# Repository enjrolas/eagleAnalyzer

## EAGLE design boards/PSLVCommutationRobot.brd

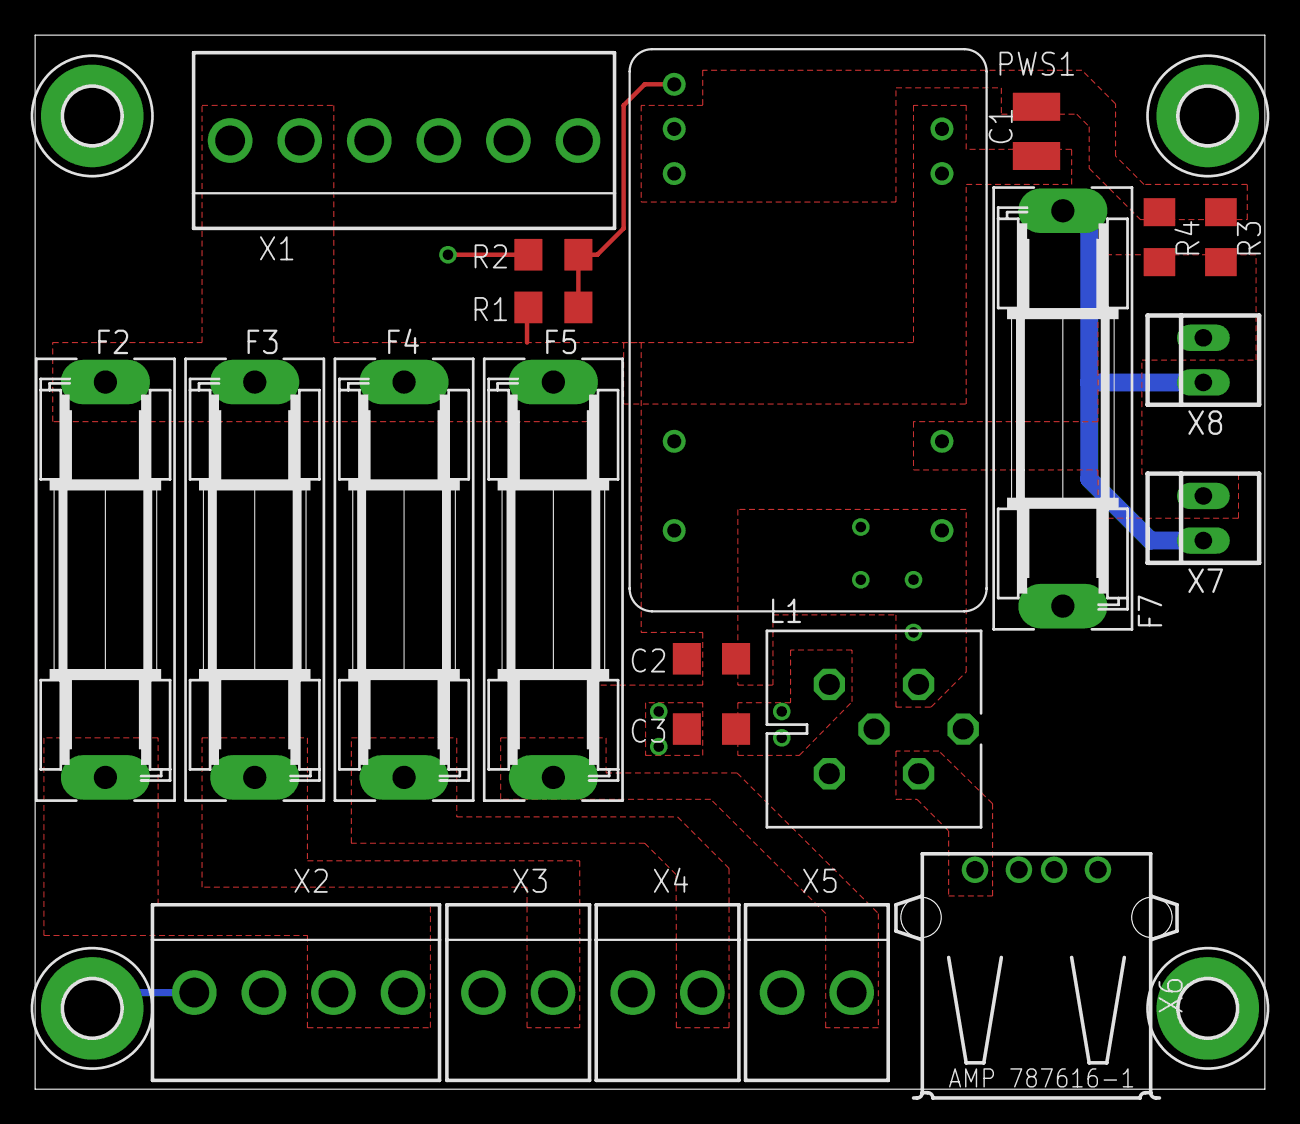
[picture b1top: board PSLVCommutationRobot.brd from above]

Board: 2 copper layers, 70.0 x 60.0 mm, 26 parts (0 on the bottom side), 12 nets.

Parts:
C1: 1uF 50V; C1210
C2, C3: 1nF 2KV; C1206
F2, F3, F4, F5: FH-102; SH22,5
F7: SH22,5
H1, H2, H3, H4: MOUNT-PAD-ROUND3.3; 3,3-PAD
L1: BNX002
PWS1: TEN_8-2411; TRACO_TEN_8_SERIE
R1, R2: 1M 5%; R1206
R3, R4: 0R; R1206
X1: 09-65-2068; MOLEX_09-65-2068
X2: 09-65-2048; MOLEX_09-65-2048
X3, X4, X5: 09-65-2028; MOLEX_09-65-2028
X6: USB type A; USB
X7, X8: 22-23-2021

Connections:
+5V: L1.CB, X6.1
+5V_OUT: C2.2, F7.1, L1.B, PWS1.14
+24V_IN: C1.1, C2.1, F2.1, F3.1, F4.1, F5.1, PWS1.22, PWS1.23, R1.1, X1.1, X1.2
GND: C1.2, C3.1, H4.B3,3, PWS1.2, PWS1.3, R2.2, R3.1, R4.1, X1.3, X1.4, X2.3, X2.4, X3.2, X4.2, X5.2
GND1: L1.CG, L1.CG1, L1.CG2, X6.4
GND_OUT: C3.2, L1.PSG, PWS1.16, R3.2, R4.2, X7.2, X8.2
unnamed: PWS1.1, R1.2, R2.1
unnamed: F2.2, X2.1, X2.2
unnamed: F3.2, X3.1
unnamed: F7.2, X7.1, X8.1
unnamed: F5.2, X5.1
unnamed: F4.2, X4.1

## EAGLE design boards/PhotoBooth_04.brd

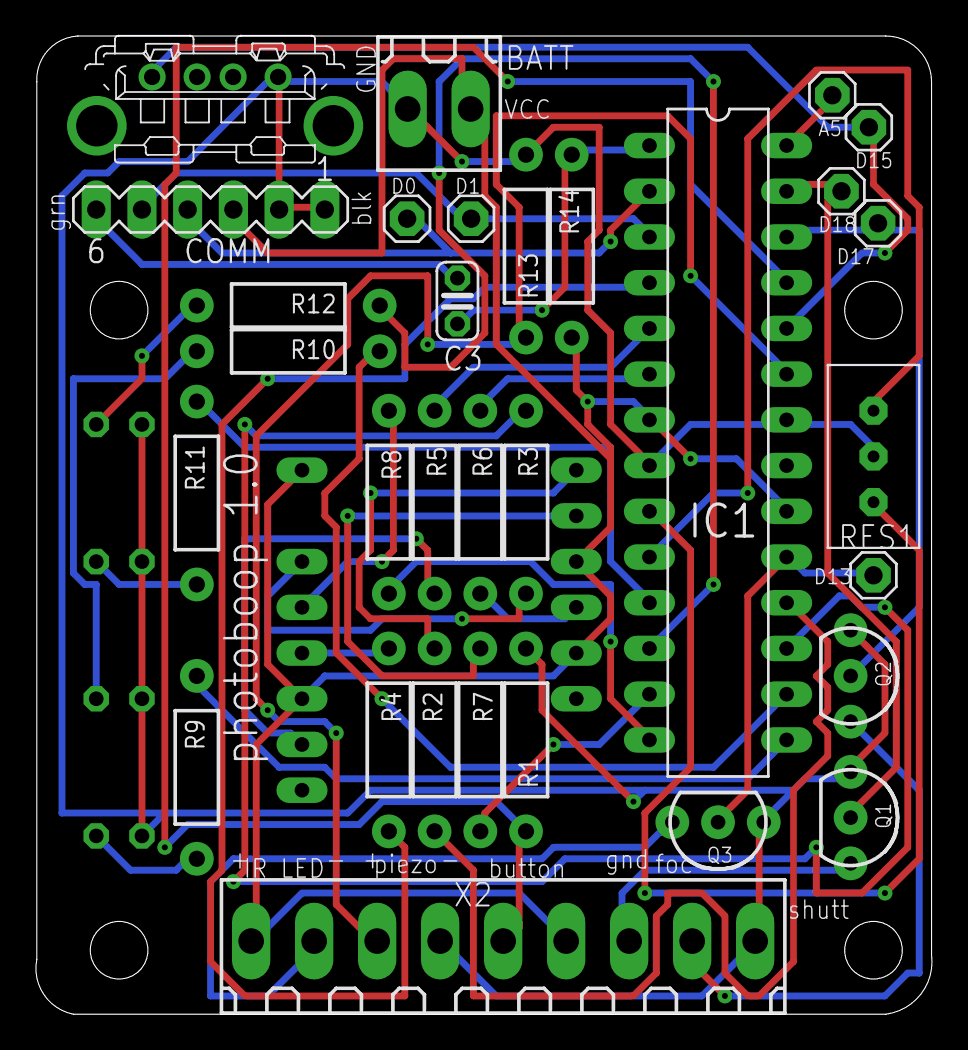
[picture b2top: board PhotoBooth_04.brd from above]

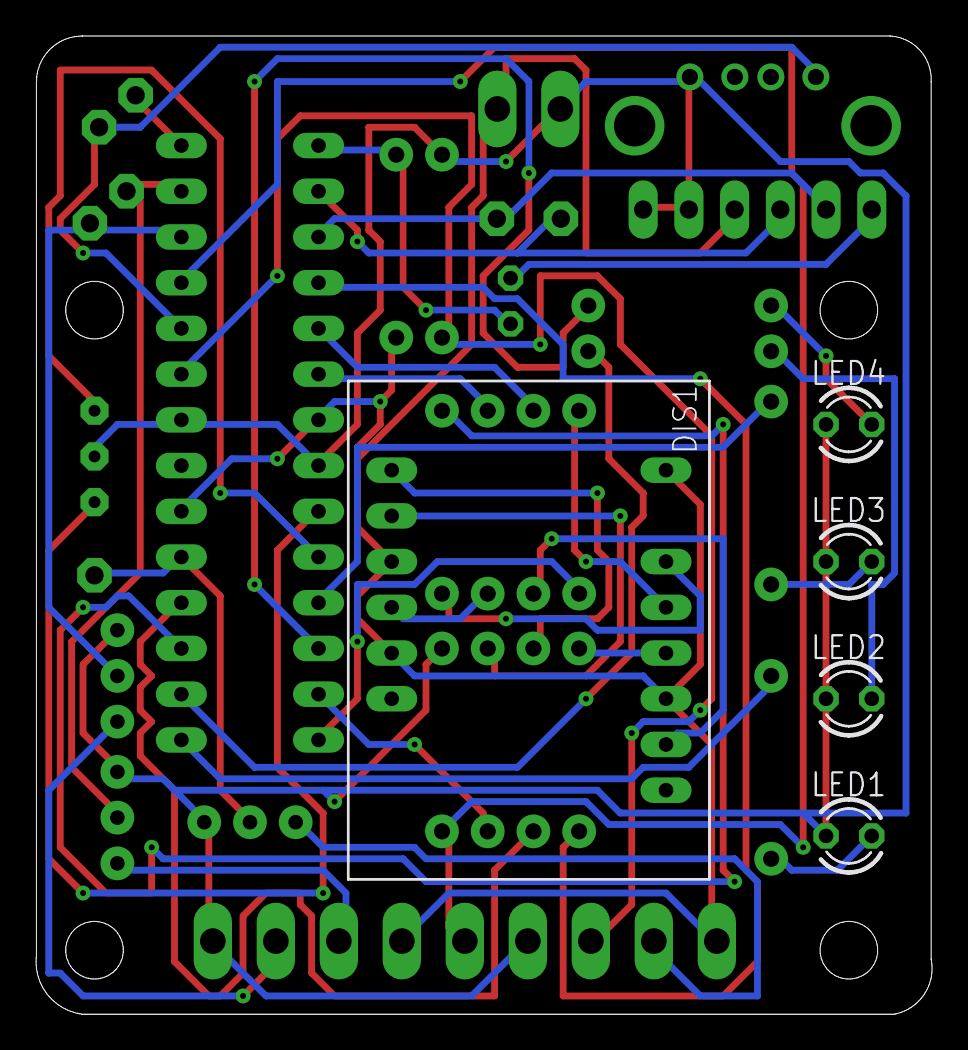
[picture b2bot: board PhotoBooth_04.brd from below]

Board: 2 copper layers, 49.8 x 54.3 mm, 36 parts (5 on the bottom side), 40 nets.

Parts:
A5: 1X01
BATT: 180-2
C3: 0.1uF; C025-024X044
COMM: MA06-1
D0, D1, D13, D15, D17, D18: 1X01
DIS1: HD-N105; HDSP-Q
IC1: ATMEGA328-P; DIL28-3
LED1, LED2, LED3, LED4: LED3MM
Q1, Q2, Q3: 2N3904; TO-92-AMMO
R1, R14: 10k; AXIAL-0.4
R2, R3, R4, R5, R6, R7, R8, R9, R10, R11, R12: 220; AXIAL-0.4
R13: 10M; AXIAL-0.4
RES1: RESONZTT
X1: USBVX; KUSBVX
X2: 180-9

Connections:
A_SEGMENT: IC1.18, R2.P$2
BUTTON: IC1.25, R1.P$1, X2.5
B_SEGMENT: IC1.17, R3.P$2
CAMERA: D15.1, IC1.24, X1.1
C_SEGMENT: IC1.4, R4.P$2
DIR: C3.1, COMM.6
D_SEGMENT: IC1.5, R5.P$2
E_SEGMENT: IC1.6, R6.P$2
F_SEGMENT: IC1.13, R7.P$2
GND: BATT.2, COMM.1, COMM.2, IC1.8, IC1.22, LED1.K, LED2.K, LED3.K, LED4.K, Q1.1, Q2.1, Q3.1, R1.P$2, R13.P$2, RES1.2, X1.4, X2.4, X2.9
G_SEGMENT: IC1.14, R8.P$2
IR_LED: D13.1, IC1.19, Q3.2
unnamed: LED1.A, R9.P$2
unnamed: DIS1.14, R8.P$1
unnamed: DIS1.3, R7.P$1
unnamed: DIS1.5, R6.P$1
unnamed: DIS1.11, R5.P$1
unnamed: DIS1.13, R4.P$1
unnamed: LED2.A, R10.P$2
unnamed: DIS1.15, R3.P$1
unnamed: DIS1.2, R2.P$1
unnamed: LED3.A, R11.P$2
unnamed: LED4.A, R12.P$2
unnamed: Q1.3, X2.7
unnamed: IC1.10, RES1.1
unnamed: IC1.9, RES1.3
unnamed: C3.2, IC1.1, R14.P$2
unnamed: A5.1, IC1.28
unnamed: Q2.3, X2.8
unnamed: Q3.3, X2.2
unnamed: COMM.4, D0.1, IC1.2
unnamed: COMM.5, D1.1, IC1.3
NUM1: IC1.15, R9.P$1
NUM2: IC1.16, R10.P$1
NUM3: IC1.11, R11.P$1
NUM4: IC1.12, R12.P$1
PIEZO: IC1.23, R13.P$1, X2.3
VCC: BATT.1, COMM.3, DIS1.4, DIS1.6, DIS1.12, DIS1.17, IC1.7, IC1.20, R14.P$1, X2.1, X2.6
WIRED_FOCUS: D17.1, IC1.26, Q2.2
WIRED_SHUTTER: D18.1, IC1.27, Q1.2

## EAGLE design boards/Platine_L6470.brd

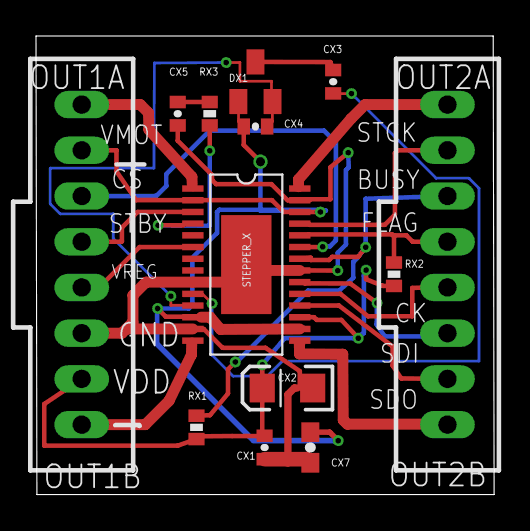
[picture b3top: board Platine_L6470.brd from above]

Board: 2 copper layers, 25.5 x 25.5 mm, 13 parts (0 on the bottom side), 21 nets.

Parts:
CX1: 0.1uF; 0402-CAP
CX2: 10uF; EIA3216
CX3, CX4, CX5: 10nF; 0402-CAP
CX7: 0.22uF; 0603-CAP
DX1: BAV99; SOT23
RX1, RX2: 10k; 0402-RES
RX3: 100; 0402-RES
STEPPER_X: L6470; HTSSOP28
X1, X2: C-GRID-08-70543; 70543-08

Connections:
BUSYN: RX1.1, STEPPER_X.22, X2.3
CK: STEPPER_X.19, X2.5
CSN: STEPPER_X.23, X1.3
FLAGN: RX2.1, STEPPER_X.24, X2.4
GND: CX1.2, CX2.C, CX5.2, CX7.2, STEPPER_X.9, STEPPER_X.13, STEPPER_X.21, STEPPER_X.27, STEPPER_X.29, X1.6
unnamed: CX3.2, STEPPER_X.10
unnamed: CX3.1, DX1.3
unnamed: CX4.1, DX1.2, STEPPER_X.11
unnamed: RX3.1, STEPPER_X.4
OUT1A: STEPPER_X.1, X1.1
OUT1B: STEPPER_X.14, X1.8
OUT2A: STEPPER_X.28, X2.1
OUT2B: STEPPER_X.15, X2.8
SDI: STEPPER_X.20, X2.6
SDO: STEPPER_X.18, X2.7
STANDBY: STEPPER_X.3, X1.4
STCK: STEPPER_X.25, X2.2
SW: CX5.1, RX3.2
VDD: CX1.1, CX2.A, RX1.2, RX2.2, STEPPER_X.17, X1.7
VMOT: CX4.2, CX7.1, DX1.1, STEPPER_X.2, STEPPER_X.12, STEPPER_X.16, STEPPER_X.26, X1.2
VREG: STEPPER_X.6, X1.5

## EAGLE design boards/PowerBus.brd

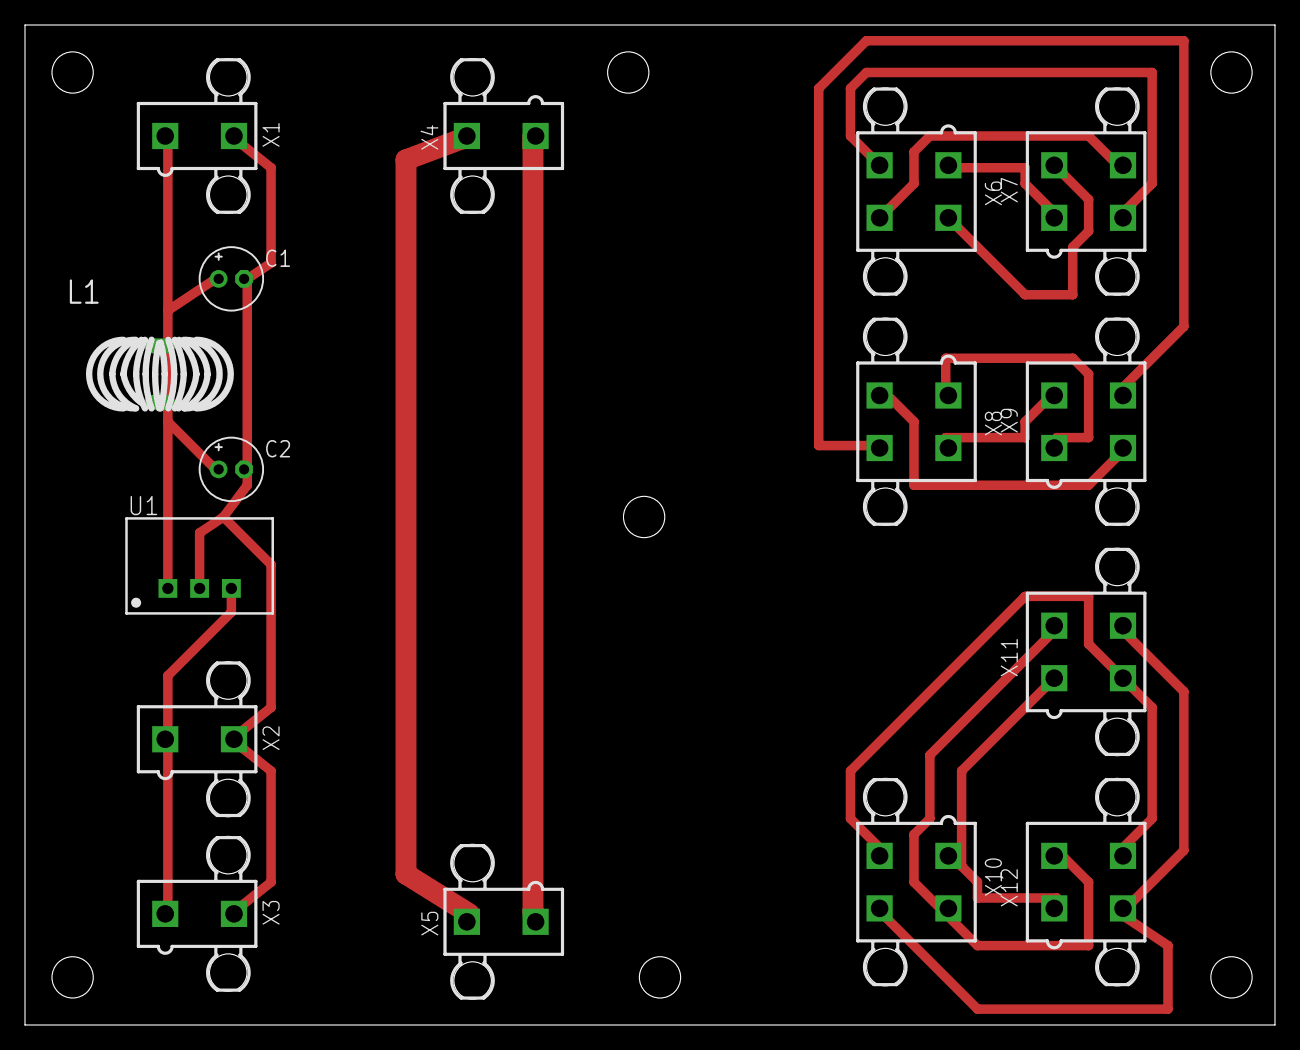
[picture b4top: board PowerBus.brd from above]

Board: 2 copper layers, 100.0 x 80.0 mm, 23 parts (0 on the bottom side), 17 nets.

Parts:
C1, C2: 4.7uF/50V; E2-5
L1: 8.2uH/.02ohm/2A; MCAP103722016A-8R2MU
U1: TSR_1-24120; TSR-1
U$1, U$2, U$3, U$4, U$5, U$6, U$7: STAND-OFF
X1, X2, X3, X4, X5: 5566-2
X6, X7, X8, X9, X10, X11, X12: 5566-4

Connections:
GND: C1.-, C2.-, U1.2, X1.2, X2.2, X3.2
unnamed: X6.1, X7.1
unnamed: X6.2, X7.2
unnamed: X6.3, X7.3
unnamed: X6.4, X7.4
unnamed: X4.1, X5.1
unnamed: X4.2, X5.2
unnamed: X8.1, X9.1
unnamed: X8.2, X9.2
unnamed: X8.3, X9.3
unnamed: X8.4, X9.4
unnamed: X10.1, X11.1, X12.1
unnamed: X10.2, X11.2, X12.2
unnamed: X10.3, X11.3, X12.4
unnamed: X10.4, X11.4, X12.3
VI: C1.+, C2.+, L1.1, L1.2, U1.1, X1.1
VO: U1.3, X2.1, X3.1

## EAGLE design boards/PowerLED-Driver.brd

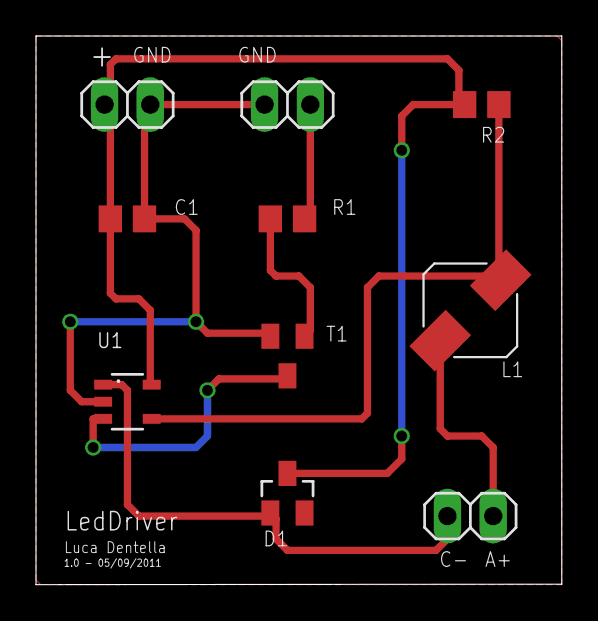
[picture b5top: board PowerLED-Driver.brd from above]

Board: 2 copper layers, 29.2 x 30.5 mm, 10 parts (0 on the bottom side), 8 nets.

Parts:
C1: 1uF; C0805
D1: ZLLS1000; DIODE_SOT23
JP1: IN; 1X02
JP2: LED; 1X02
JP3: CTRL; 1X02
L1: 68uH; JENWILLY_CUSTOM_ELL5PS_INDUCTOR
R1: 3.3k; R0805
R2: 0.33; R0805
T1: BC848; SOT23
U1: ZXLD1350; JENWILLY_CUSTOM_SOT23-5

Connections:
+12V: C1.1, D1.3, JP1.2, R2.2, U1.5
GND: C1.2, JP1.1, JP3.1, T1.2, U1.2
unnamed: JP3.2, R1.2
unnamed: R1.1, T1.1
unnamed: T1.3, U1.3
unnamed: D1.1, JP2.2, U1.1
unnamed: L1.P$1, R2.1, U1.4
unnamed: JP2.1, L1.P$2

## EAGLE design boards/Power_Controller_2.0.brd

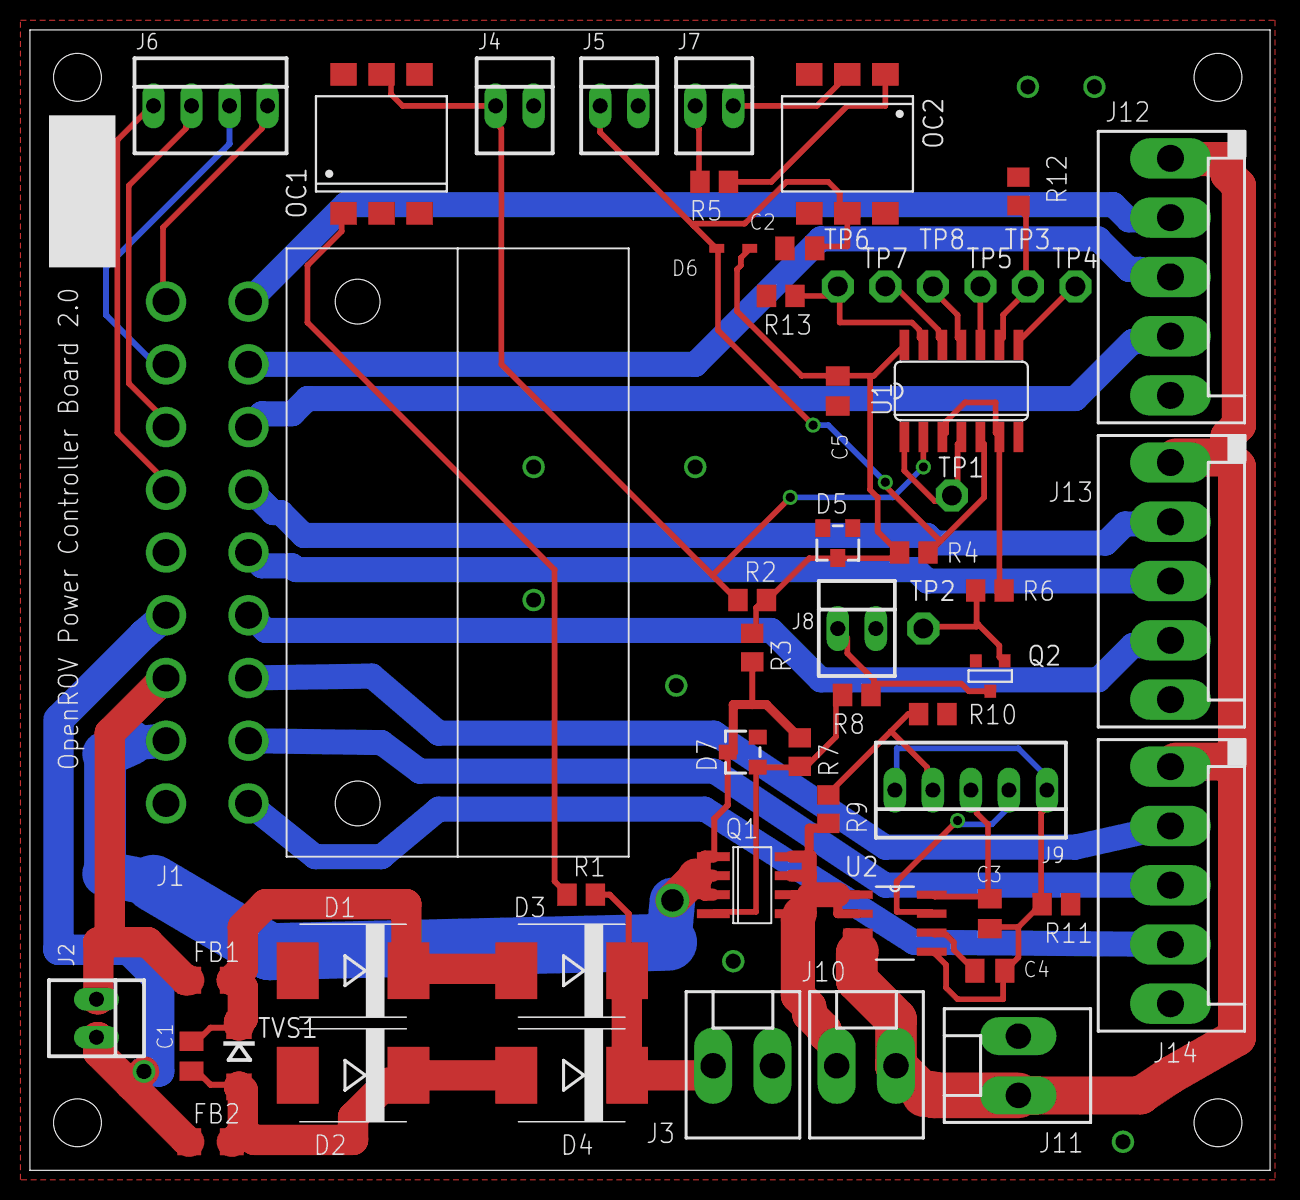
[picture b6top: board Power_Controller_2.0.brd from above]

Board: 2 copper layers, 82.9 x 76.2 mm, 56 parts (0 on the bottom side), 45 nets.

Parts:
C1, C2, C3, C4, C5: 0.1 uF; C0805K
D1, D2, D3, D4: B560; SMC
D5, D7: BZX84B16; TO236
D6: SDM10K45; SOD323
FB1, FB2: HI1206T161R-10; R1206
J1: MINI-FIT-JR-18-PEGS
J2, J4, J5, J7, J8: 22-23-2021
J3, J10, J11: KK-156-2
J6: 22-23-2041
J9: 22-23-2051
J12, J13, J14: ESC-PADS
OC1, OC2: 4N33S; DIL6-SMD
Q1: SI4425DDY; SO8
Q2: 2N7002; SOT-23
R1, R7: 10K; R0805
R2, R4: 27K; R0805
R3, R8: 1K; R0805
R5: 3.9K; R0805
R6, R12, R13: 0; R0805
R9, R10, R11: DNP; R0805
TP1, TP2, TP3, TP4, TP5, TP6, TP7, TP8: TPPAD1-13; P1-13
TVS1: SMAJ45CA; DO214AC
U1: CD4011BM; SO14
U2: ACS712ELCTR-20A-T; SOIC127P600X175-8N

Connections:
1A: J1.1, J12.2
1B: J1.2, J12.3
1C: J1.3, J12.4
2A: J1.4, J13.2
2B: J1.5, J13.3
2C: J1.6, J13.4
3A: J1.7, J14.2
3B: J1.8, J14.3
3C: J1.9, J14.4
BATTERY+: D7.C, J1.17, Q1.1, Q1.2, Q1.3, R3.2, R7.1
GND: C2.2, C5.2, D1.A, D2.A, D5.A, J1.18, J3.2, J4.2, J5.2, J8.2, J11.2, J12.5, J13.5, J14.5, OC1.2, OC1.4, OC2.4, Q2.2, R10.1, R11.1, R12.1, R13.1, U1.7
I2C_GND: J1.10, J6.4
I2C_SCL: J1.12, J6.2
I2C_SDA: J1.11, J6.3
I2C_VCC: J1.13, J6.1
unnamed: R6.1, U1.3, U1.6
unnamed: OC2.1, R5.1
unnamed: R12.2, TP3.TP, U1.9
unnamed: R13.2, TP6.TP, U1.13
unnamed: TP5.TP, U1.10
unnamed: TP8.TP, U1.11
unnamed: D7.A, Q1.4, R7.2, R8.2
unnamed: Q2.3, R6.2, TP2.TP
unnamed: J7.2, OC2.2
unnamed: TP4.TP, U1.8
unnamed: J8.1, Q2.1, R8.1
unnamed: TP7.TP, U1.12
unnamed: J10.1, Q1.5, Q1.6, Q1.7, Q1.8, R9.2, U2.1, U2.2
unnamed: C1.1, D1.C, D3.A, FB1.2, TVS1.C
unnamed: C1.2, D2.C, D4.A, FB2.2, TVS1.A
unnamed: OC1.1, R1.1
unnamed: J9.4, R9.1, R10.2
unnamed: C3.1, J9.3, U2.8
unnamed: C4.1, U2.6
unnamed: C3.2, C4.2, J9.1, J9.5, R11.2, U2.5
unnamed: J9.2, U2.7
POWER_OFF*: C2.1, D6.2, J5.1, OC2.5, R4.1, U1.5
POWER_ON*: J4.1, OC1.5, R2.1, U1.2
POWER_SWITCH*: TP1.TP, U1.1, U1.4
SOFT_POWER_OFF: J7.1, R5.2
TETHER_A: FB1.1, J1.16, J2.1
TETHER_B: FB2.1, J1.15, J2.2
TETHER_POWER: D3.C, D4.C, J3.1, R1.2
U1_POWER: C5.1, D5.C, D6.1, R2.2, R3.1, R4.2, U1.14
V_BAT_SWITCHED: J10.2, J11.1, J12.1, J13.1, J14.1, U2.3, U2.4

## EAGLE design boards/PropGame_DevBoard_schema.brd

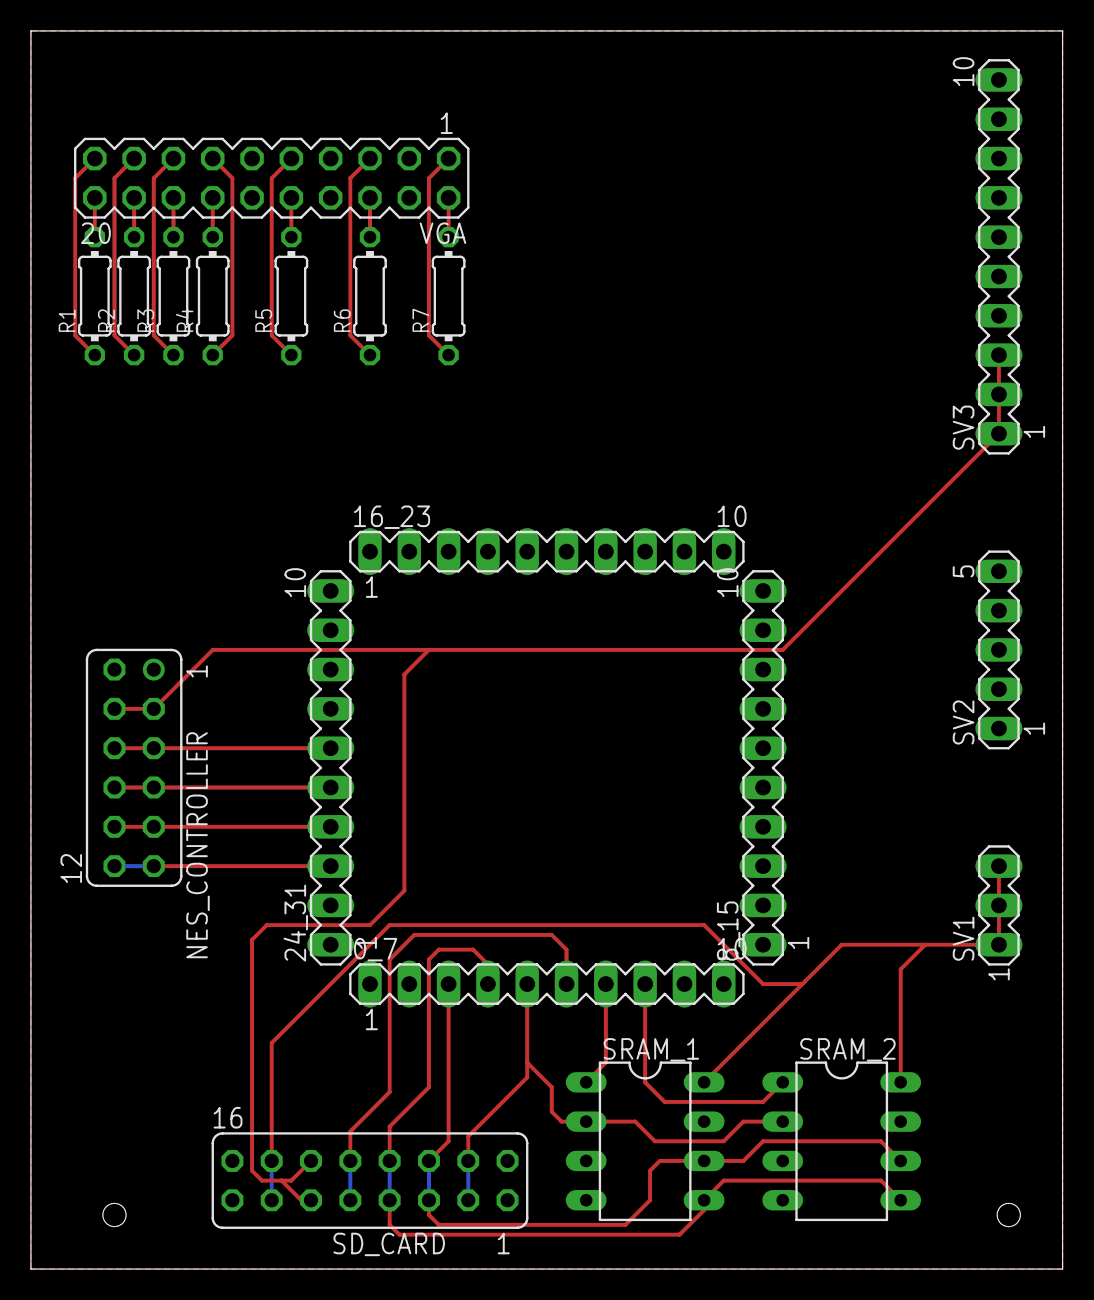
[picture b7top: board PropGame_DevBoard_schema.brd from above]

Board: 2 copper layers, 66.7 x 80.0 mm, 19 parts (0 on the bottom side), 27 nets.

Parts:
0_7, 8_15, 16_23, 24_31: MA10-1
NES_CONTROLLER: FE06-2
R1, R2, R3, R4, R5, R6, R7: 0204/7
SD_CARD: FE08-2
SRAM_1, SRAM_2: DIL08
SV1: MA03-1
SV2: MA05-1
SV3: MA10-1
VGA: MA10-2

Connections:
3V3: SD_CARD.13, SD_CARD.14, SRAM_1.8, SRAM_2.8, SV1.1, SV1.2, SV1.3
5V: NES_CONTROLLER.3, NES_CONTROLLER.4, SD_CARD.11, SD_CARD.12, SV3.1, SV3.2, SV3.3
CLK: 24_31.3, NES_CONTROLLER.11, NES_CONTROLLER.12
CS_1: 0_7.6, SD_CARD.9, SD_CARD.10
CS_2: 0_7.7, SRAM_1.1
CS_3: 0_7.8, SRAM_2.1
DATA1: 24_31.5, NES_CONTROLLER.7, NES_CONTROLLER.8
DATA2: 24_31.6, NES_CONTROLLER.5, NES_CONTROLLER.6
GND: NES_CONTROLLER.1, NES_CONTROLLER.2, SD_CARD.1, SD_CARD.2, SD_CARD.15, SD_CARD.16, SRAM_1.4, SRAM_2.4, SV2.1, SV2.2, SV2.3, SV2.4, SV2.5, SV3.4, SV3.5, SV3.6, SV3.7, SV3.8, SV3.9, SV3.10
LATCH: 24_31.4, NES_CONTROLLER.9, NES_CONTROLLER.10
MISO: 0_7.5, SD_CARD.3, SD_CARD.4, SRAM_1.2, SRAM_2.2
MOSI: 0_7.4, SD_CARD.7, SD_CARD.8, SRAM_1.5, SRAM_2.5
unnamed: R1.2, VGA.20
unnamed: R2.2, VGA.18
unnamed: R3.2, VGA.16
unnamed: R4.2, VGA.14
unnamed: R5.2, VGA.10
unnamed: R6.2, VGA.6
unnamed: R7.2, VGA.2
SCK: 0_7.3, SD_CARD.5, SD_CARD.6, SRAM_1.6, SRAM_2.6
W_1: R1.1, VGA.19
W_2: R2.1, VGA.17
W_3: R3.1, VGA.15
W_4: R4.1, VGA.13
W_5: R5.1, VGA.9
W_6: R6.1, VGA.5
W_7: R7.1, VGA.1

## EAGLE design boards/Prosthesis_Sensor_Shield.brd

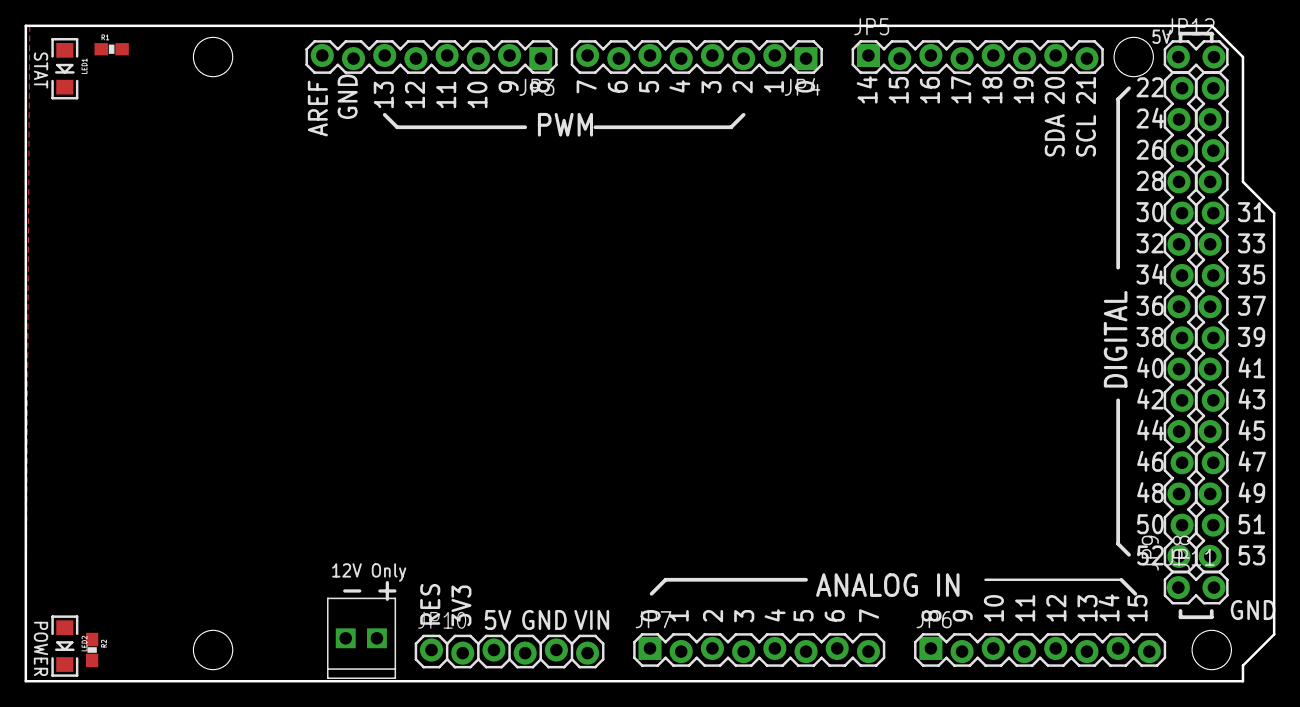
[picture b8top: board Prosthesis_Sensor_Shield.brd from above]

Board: 2 copper layers, 101.6 x 53.3 mm, 15 parts (0 on the bottom side), 7 nets, no tracks yet.

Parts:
JP3, JP4, JP5, JP6, JP7: 1X08_LOCK
JP8, JP9: M16LOCK; 1X16_LOCK
JP10: 1X06_LOCK
JP11, JP12: 1X02_LOCK
LED1: Green; LED-1206
LED2: Red; LED-1206
PWR: M022.54MM_SCREWTERM; 1X02_2.54_SCREWTERM
R1, R2: 330; 0603-RES

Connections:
5V: JP10.3, R2.2
5V@1: JP12.1, JP12.2
D13: JP3.6, R1.2
GND: JP3.7, JP10.4, JP10.5, JP11.1, JP11.2, LED1.C, LED2.C, PWR.P1
unnamed: LED2.A, R2.1
unnamed: LED1.A, R1.1
VIN: JP10.6, PWR.P2

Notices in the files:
parts and their libraries:
SparkFun-Electromechanical: Licensing: CC v3.0 Share-Alike You are welcome to use this library for commercial purposes.
